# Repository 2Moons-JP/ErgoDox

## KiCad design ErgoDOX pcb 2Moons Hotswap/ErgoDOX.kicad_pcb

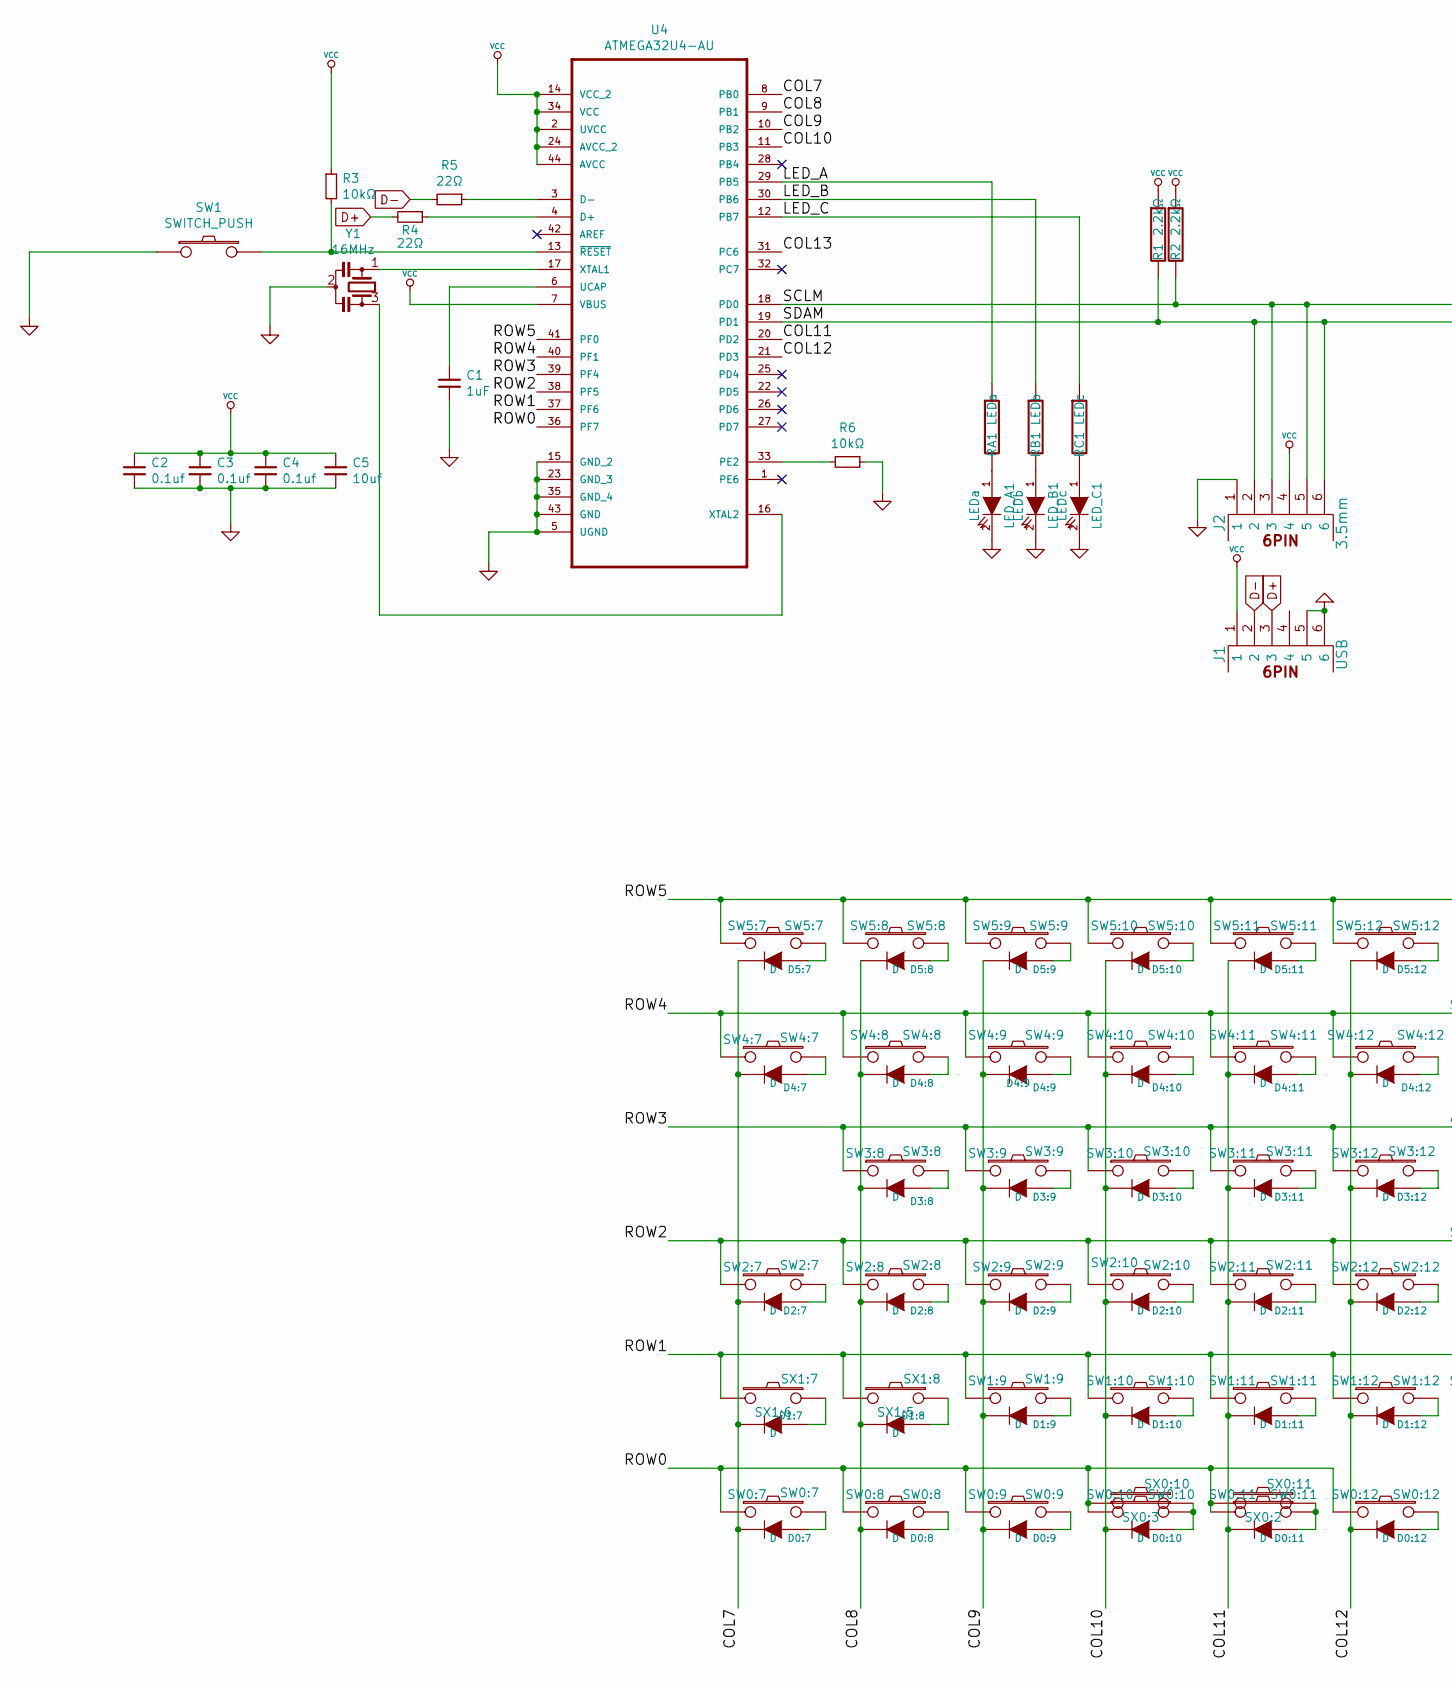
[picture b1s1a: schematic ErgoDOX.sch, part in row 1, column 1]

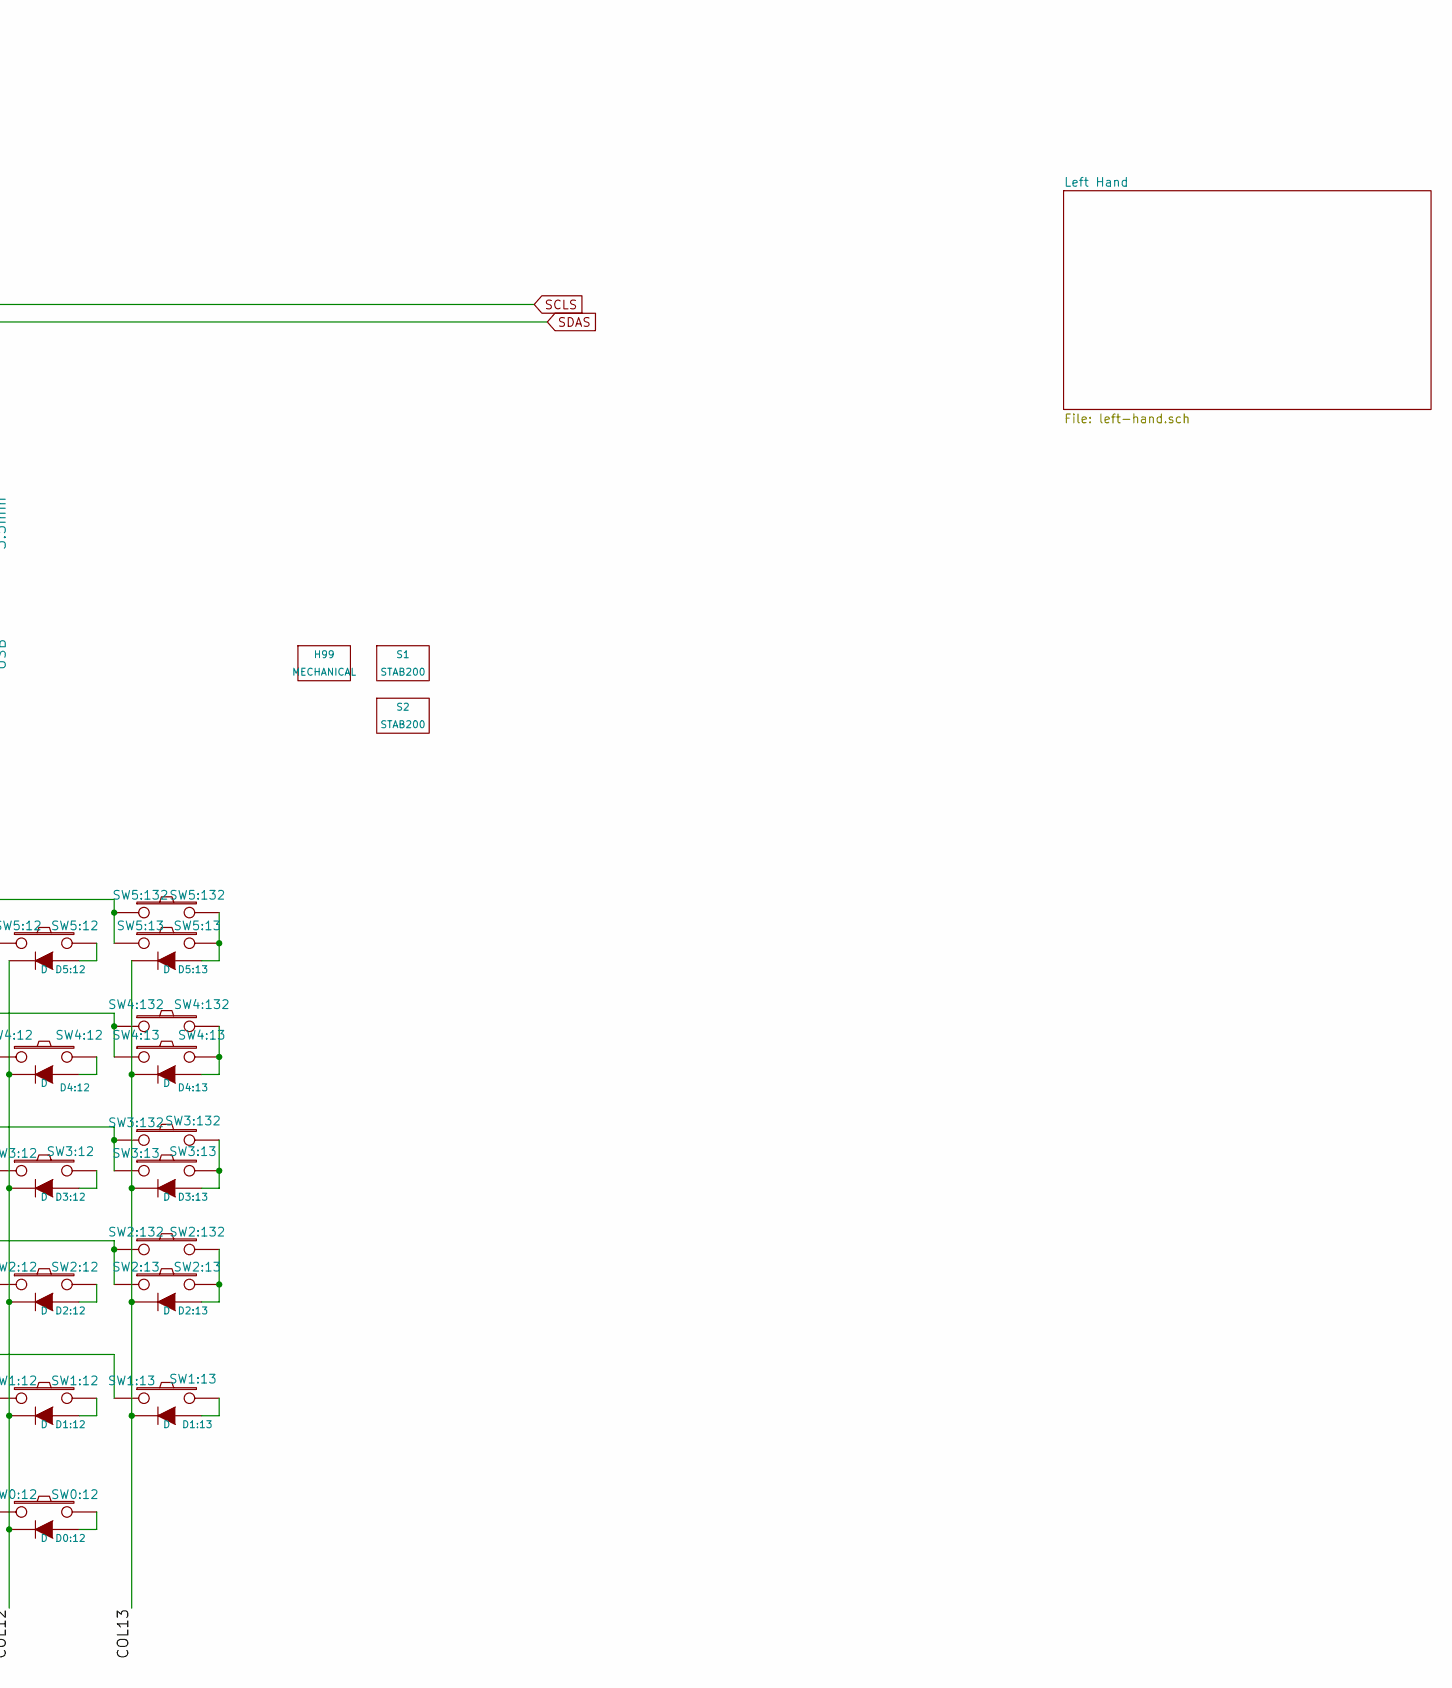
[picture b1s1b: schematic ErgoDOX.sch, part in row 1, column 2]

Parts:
C1: 1uF; C_0603_1608Metric; Part# CL10A105KP8NNNC; LCSC Part# C26413
C2, C3, C4: 0.1uf; C_0603_1608Metric; Part# GRM188R71H104KA93D; LCSC Part# C77055
C5: 10uf; C_0603_1608Metric; Part# JMK107ABJ106MA-T; LCSC Part# C268008
D0:7, D0:8, D0:9, D0:10, D0:11, D0:12, D1:7, D1:8, D1:9, D1:10, D1:11, D1:12, D1:13, D2:7, D2:8, D2:9, D2:10, D2:11, D2:12, D2:13, D3:8, D3:9, D3:10, D3:11, D3:12, D3:13, D4:7, D4:8, D4:10, D4:11, D4:12, D4:13, D5:7, D5:8, D5:9, D5:10, D5:11, D5:12, D5:13: D; D3_SMD_v2_copy; Part# 1N4148W; LCSC Part# C81598
D4:9: D4:9; D3_SMD_v2_copy; Part# 1N4148W; LCSC Part# C81598
H99: MECHANICAL
J1: USB; USBMINImod; Part# 548190519; LCSC Part# C240850
J2: 3.5mm; 4pin35mmAudio; Part# CP-43514-ND; LCSC Part# SJ-43514
LED_A1: LEDa; MX_LED
LED_B1: LEDb; MX_LED
LED_C1: LEDc; MX_LED
R1, R2: 2.2kΩ; R_0603_1608Metric; Part# 0603WAF2201T5E; LCSC Part# C4190
R3, R6: 10kΩ; R_0603_1608Metric; Part# 0603WAF1002T5E; LCSC Part# C25804
R4, R5: 22Ω; R_0603_1608Metric; Part# RS-03K220JT; LCSC Part# C96423
RA1: LEDa; RESISTOR
RB1: LEDb; RESISTOR
RC1: LEDc; RESISTOR
S1, S2: STAB200
SW0:7: SW0:7; MXOnly-1U-Hotswap
SW0:8: SW0:8; MXOnly-1U-Hotswap
SW0:9: SW0:9; MXOnly-1U-Hotswap
SW0:10: SW0:10; MXOnly-2U-Hotswap
SW0:11: SW0:11; MXOnly-2U-Hotswap-ReversedStabilizers
SW0:12: SW0:12; MXOnly-1U-Hotswap
SW1: SWITCH_PUSH; SKQG-1155865; Part# RS-187R05A2-DSMTRT; LCSC Part# C221929
SW1:9: SW1:9; MXOnly-1U-Hotswap
SW1:10: SW1:10; MXOnly-1U-Hotswap
SW1:11: SW1:11; MXOnly-1U-Hotswap
SW1:12: SW1:12; MXOnly-1U-Hotswap
SW1:13: SW1:13; MXOnly-1U-Hotswap
SW2:7: SW2:7; MXOnly-1U-Hotswap
SW2:8: SW2:8; MXOnly-1U-Hotswap
SW2:9: SW2:9; MXOnly-1U-Hotswap
SW2:10: SW2:10; MXOnly-1U-Hotswap
SW2:11: SW2:11; MXOnly-1U-Hotswap
SW2:12: SW2:12; MXOnly-1U-Hotswap
SW2:13: SW2:13; MXOnly-1.5U-Hotswap
SW2:132: SW2:132; MXOnly-1U-Hotswap
SW3:8: SW3:8; MXOnly-1U-Hotswap
SW3:9: SW3:9; MXOnly-1U-Hotswap
SW3:10: SW3:10; MXOnly-1U-Hotswap
SW3:11: SW3:11; MXOnly-1U-Hotswap
SW3:12: SW3:12; MXOnly-1U-Hotswap
SW3:13: SW3:13; MXOnly-1.5U-Hotswap
SW3:132: SW3:132; MXOnly-1U-Hotswap
SW4:7: SW4:7; MXOnly-1U-Hotswap
SW4:8: SW4:8; MXOnly-1U-Hotswap
SW4:9: SW4:9; MXOnly-1U-Hotswap
SW4:10: SW4:10; MXOnly-1U-Hotswap
SW4:11: SW4:11; MXOnly-1U-Hotswap
SW4:12: SW4:12; MXOnly-1U-Hotswap
SW4:13: SW4:13; MXOnly-1.5U-Hotswap
SW4:132: SW4:132; MXOnly-1U-Hotswap
SW5:7: SW5:7; MXOnly-1U-Hotswap
SW5:8: SW5:8; MXOnly-1U-Hotswap
SW5:9: SW5:9; MXOnly-1U-Hotswap
SW5:10: SW5:10; MXOnly-1U-Hotswap
SW5:11: SW5:11; MXOnly-1U-Hotswap
SW5:12: SW5:12; MXOnly-1U-Hotswap
SW5:13: SW5:13; MXOnly-1.5U-Hotswap
SW5:132: SW5:132; MXOnly-1U-Hotswap
SX0:10: SX0:3; MXOnly-1U-Hotswap
SX0:11: SX0:2; MXOnly-1U-Hotswap
SX1:7: SX1:6; MXOnly-1U-Hotswap
SX1:8: SX1:5; MXOnly-1U-Hotswap
U4: ATMEGA32U4-AU; Part# ATMEGA32U4-AU; LCSC Part# C44854
Y1: 16MHz; Resonator_SMD_muRata_CSTxExxV-3Pin_3.0x1.1mm_HandSoldering_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; Part# CSTNE16M0V530000R0; LCSC Part# C341521

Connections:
/COL7: D0:7.2 (K), D1:7.2 (K), D2:7.2 (K), D4:7.2 (K), D5:7.2 (K), U4.8 (PB0)
/COL8: D0:8.2 (K), D1:8.2 (K), D2:8.2 (K), D3:8.2 (K), D4:8.2 (K), D5:8.2 (K), U4.9 (PB1)
/COL9: D0:9.2 (K), D1:9.2 (K), D2:9.2 (K), D3:9.2 (K), D4:9.2 (K), D5:9.2 (K), U4.10 (PB2)
/COL10: D0:10.2 (K), D1:10.2 (K), D2:10.2 (K), D3:10.2 (K), D4:10.2 (K), D5:10.2 (K), U4.11 (PB3)
/COL11: D0:11.2 (K), D1:11.2 (K), D2:11.2 (K), D3:11.2 (K), D4:11.2 (K), D5:11.2 (K), U4.20 (PD2)
/COL12: D0:12.2 (K), D1:12.2 (K), D2:12.2 (K), D3:12.2 (K), D4:12.2 (K), D5:12.2 (K), U4.21 (PD3)
/COL13: D1:13.2 (K), D2:13.2 (K), D3:13.2 (K), D4:13.2 (K), D5:13.2 (K), U4.31 (PC6)
/LED_A: RA1.1, U4.29 (PB5)
/LED_B: RB1.1, U4.30 (PB6)
/LED_C: RC1.1, U4.12 (PB7)
/ROW0: SW0:7.1, SW0:8.1, SW0:9.1, SW0:10.1, SW0:11.1, SW0:12.1, SX0:10.1, SX0:11.1, U4.36 (PF7)
/ROW1: SW1:9.1, SW1:10.1, SW1:11.1, SW1:12.1, SW1:13.1, SX1:7.1, SX1:8.1, U4.37 (PF6)
/ROW2: SW2:7.1, SW2:8.1, SW2:9.1, SW2:10.1, SW2:11.1, SW2:12.1, SW2:13.1, SW2:132.1, U4.38 (PF5)
/ROW3: SW3:8.1, SW3:9.1, SW3:10.1, SW3:11.1, SW3:12.1, SW3:13.1, SW3:132.1, U4.39 (PF4)
/ROW4: SW4:7.1, SW4:8.1, SW4:9.1, SW4:10.1, SW4:11.1, SW4:12.1, SW4:13.1, SW4:132.1, U4.40 (PF1)
/ROW5: SW5:7.1, SW5:8.1, SW5:9.1, SW5:10.1, SW5:11.1, SW5:12.1, SW5:13.1, SW5:132.1, U4.41 (PF0)
D+: J1.3, R4.2; also elsewhere on the board
D-: J1.2, R5.2; also elsewhere on the board
GND: C1.2, C2.2, C3.2, C4.2, C5.2, J1.5, J1.6, J2.1, LED_A1.2 (K), LED_B1.2 (K), LED_C1.2 (K), R6.1, SW1.1, U4.5 (UGND), U4.15 (GND_2), U4.23 (GND_3), U4.35 (GND_4), U4.43 (GND), Y1.2; also elsewhere on the board
unnamed: C1.1, U4.6 (UCAP)
unnamed: D0:7.1 (A), SW0:7.2
unnamed: D0:8.1 (A), SW0:8.2
unnamed: D0:9.1 (A), SW0:9.2
unnamed: D0:10.1 (A), SW0:10.2, SX0:10.2
unnamed: D0:11.1 (A), SW0:11.2, SX0:11.2
unnamed: D0:12.1 (A), SW0:12.2
unnamed: D1:7.1 (A), SX1:7.2
unnamed: D1:8.1 (A), SX1:8.2
unnamed: D1:9.1 (A), SW1:9.2
unnamed: D1:10.1 (A), SW1:10.2
unnamed: D1:11.1 (A), SW1:11.2
unnamed: D1:12.1 (A), SW1:12.2
unnamed: D1:13.1 (A), SW1:13.2
unnamed: D2:7.1 (A), SW2:7.2
unnamed: D2:8.1 (A), SW2:8.2
unnamed: D2:9.1 (A), SW2:9.2
unnamed: D2:10.1 (A), SW2:10.2
unnamed: D2:11.1 (A), SW2:11.2
unnamed: D2:12.1 (A), SW2:12.2
unnamed: D2:13.1 (A), SW2:13.2, SW2:132.2
unnamed: D3:8.1 (A), SW3:8.2
unnamed: D3:9.1 (A), SW3:9.2
unnamed: D3:10.1 (A), SW3:10.2
unnamed: D3:11.1 (A), SW3:11.2
unnamed: D3:12.1 (A), SW3:12.2
unnamed: D3:13.1 (A), SW3:13.2, SW3:132.2
unnamed: D4:7.1 (A), SW4:7.2
unnamed: D4:8.1 (A), SW4:8.2
unnamed: D4:9.1 (A), SW4:9.2
unnamed: D4:10.1 (A), SW4:10.2
unnamed: D4:11.1 (A), SW4:11.2
unnamed: D4:12.1 (A), SW4:12.2
unnamed: D4:13.1 (A), SW4:13.2, SW4:132.2
unnamed: D5:7.1 (A), SW5:7.2
unnamed: D5:8.1 (A), SW5:8.2
unnamed: D5:9.1 (A), SW5:9.2
unnamed: D5:10.1 (A), SW5:10.2
unnamed: D5:11.1 (A), SW5:11.2
unnamed: D5:12.1 (A), SW5:12.2
unnamed: D5:13.1 (A), SW5:13.2, SW5:132.2
unnamed 115: J1.4; also elsewhere on the board
unnamed: LED_A1.1 (A), RA1.2
unnamed: LED_B1.1 (A), RB1.2
unnamed: LED_C1.1 (A), RC1.2
unnamed: R3.2, SW1.2, U4.13 (~RESET)
unnamed: R4.1, U4.4 (D+)
unnamed: R5.1, U4.3 (D-)
unnamed: R6.2, U4.33 (PE2)
unnamed: U4.16 (XTAL2), Y1.3
unnamed: U4.17 (XTAL1), Y1.1
SCLS: J2.3, J2.5, R2.2, U4.18 (PD0); also elsewhere on the board
SDAS: J2.2, J2.6, R1.2, U4.19 (PD1); also elsewhere on the board
VCC: C2.1, C3.1, C4.1, C5.1, J1.1, J2.4, R1.1, R2.1, R3.1, U4.2 (UVCC), U4.7 (VBUS), U4.14 (VCC_2), U4.24 (AVCC_2), U4.34 (VCC), U4.44 (AVCC); also elsewhere on the board

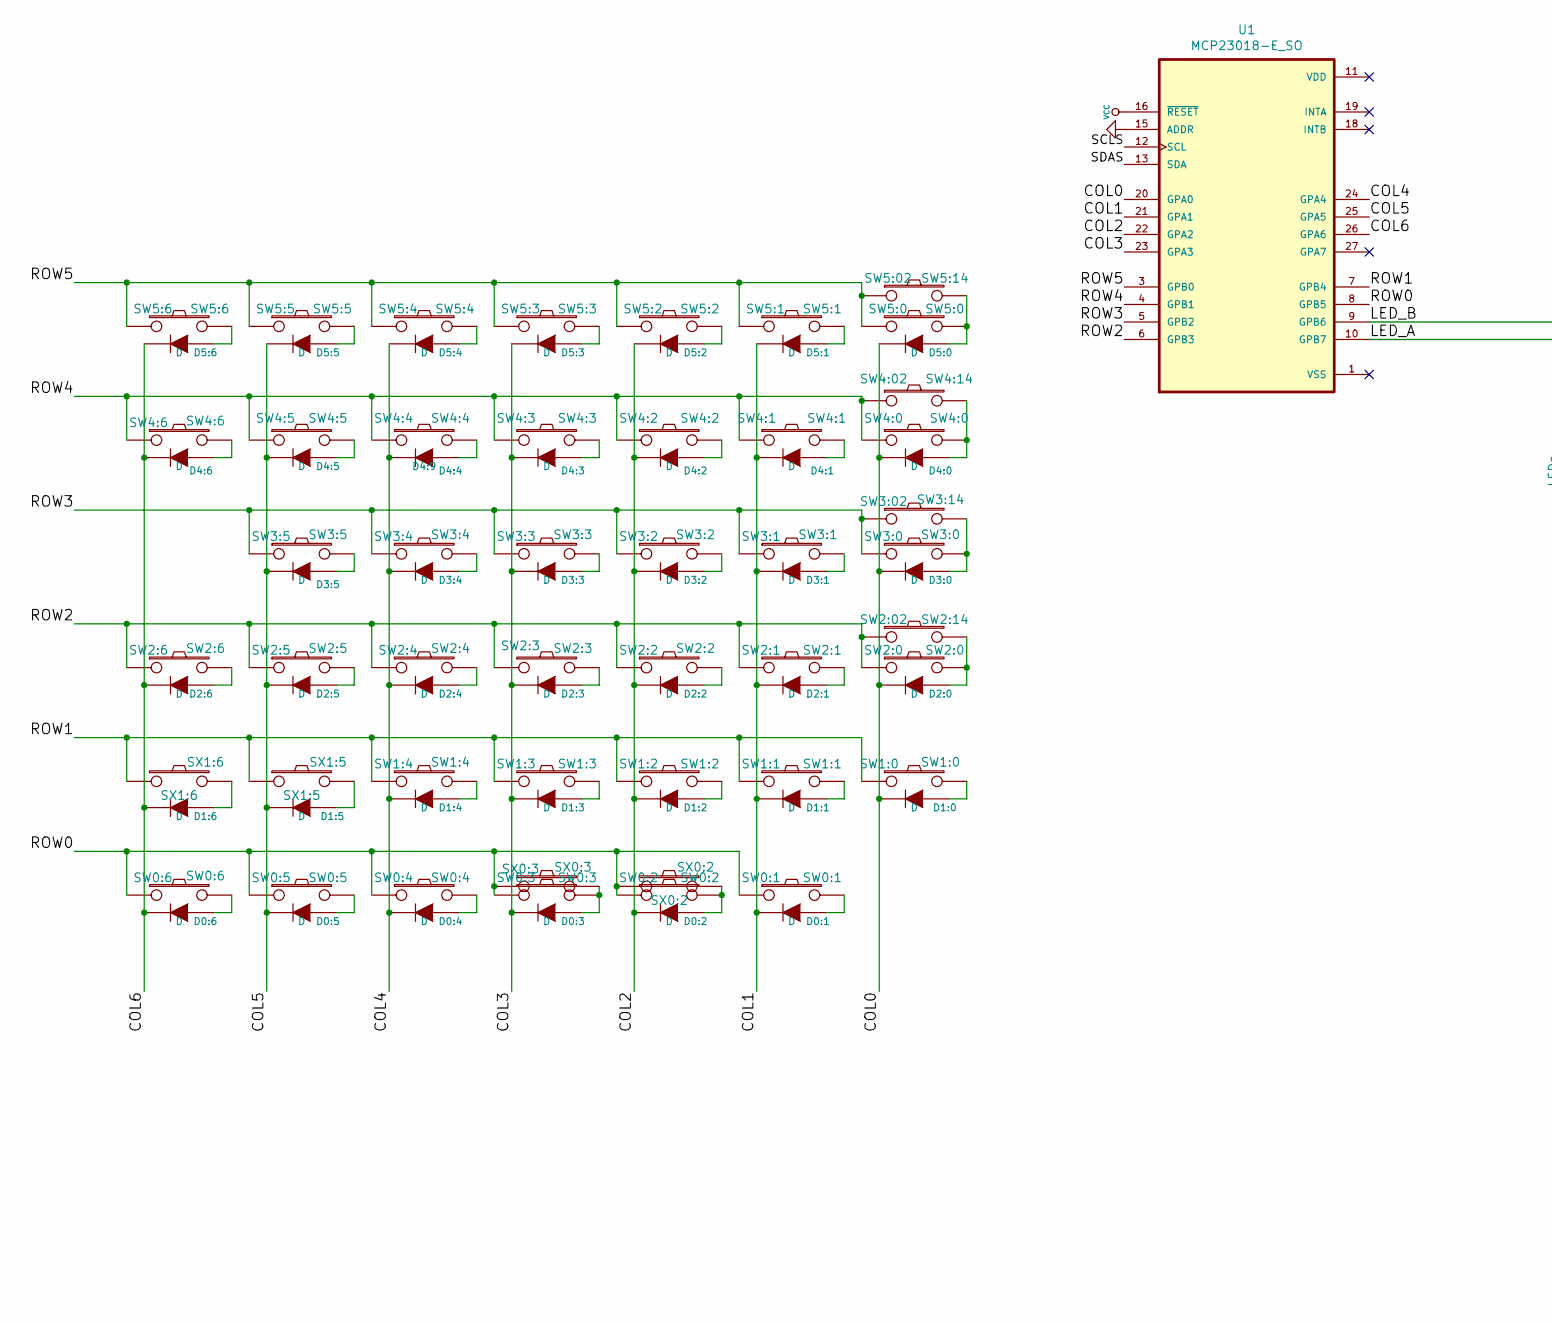
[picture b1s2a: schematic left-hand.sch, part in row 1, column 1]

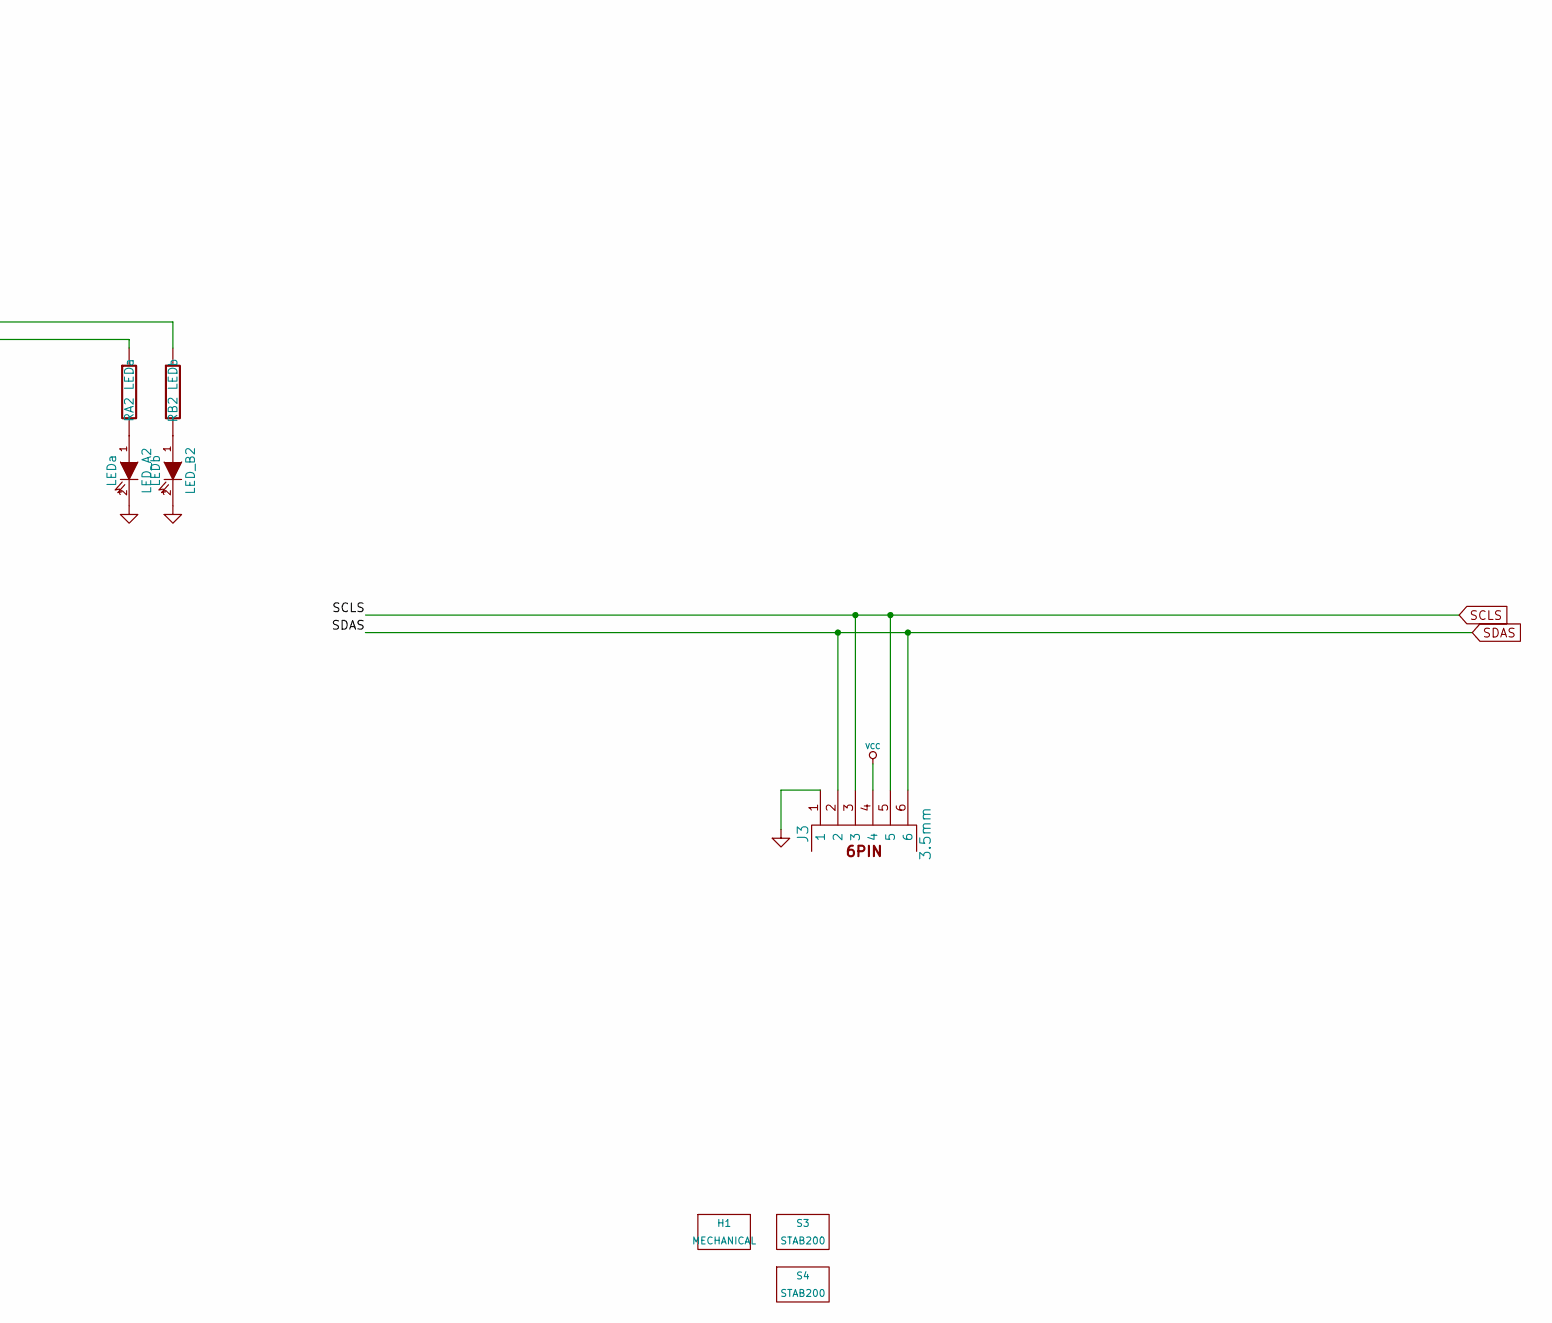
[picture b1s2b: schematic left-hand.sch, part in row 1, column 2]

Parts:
D0:1, D0:2, D0:3, D0:4, D0:5, D0:6, D1:0, D1:1, D1:2, D1:3, D1:4, D1:5, D1:6, D2:0, D2:1, D2:2, D2:3, D2:4, D2:5, D2:6, D3:0, D3:1, D3:2, D3:3, D3:4, D3:5, D4:0, D4:1, D4:2, D4:3, D4:5, D4:6, D5:0, D5:1, D5:2, D5:3, D5:4, D5:5, D5:6: D; D3_SMD_v2_copy; Part# 1N4148W; LCSC Part# C81598
D4:4: D4:9; D3_SMD_v2_copy; Part# 1N4148W; LCSC Part# C81598
H1: MECHANICAL
J3: 3.5mm; 4pin35mmAudio; Part# CP-43514-ND; LCSC Part# SJ-43514
LED_A2: LEDa; MX_LED
LED_B2: LEDb; MX_LED
RA2: LEDa; RESISTOR
RB2: LEDb; RESISTOR
S3, S4: STAB200
SW0:1: SW0:1; MXOnly-1U-Hotswap
SW0:2: SW0:2; MXOnly-2U-Hotswap-ReversedStabilizers
SW0:3: SW0:3; MXOnly-2U-Hotswap
SW0:4: SW0:4; MXOnly-1U-Hotswap
SW0:5: SW0:5; MXOnly-1U-Hotswap
SW0:6: SW0:6; MXOnly-1U-Hotswap
SW1:0: SW1:0; MXOnly-1U-Hotswap
SW1:1: SW1:1; MXOnly-1U-Hotswap
SW1:2: SW1:2; MXOnly-1U-Hotswap
SW1:3: SW1:3; MXOnly-1U-Hotswap
SW1:4: SW1:4; MXOnly-1U-Hotswap
SW2:0: SW2:0; MXOnly-1.5U-Hotswap
SW2:1: SW2:1; MXOnly-1U-Hotswap
SW2:2: SW2:2; MXOnly-1U-Hotswap
SW2:3: SW2:3; MXOnly-1U-Hotswap
SW2:4: SW2:4; MXOnly-1U-Hotswap
SW2:5: SW2:5; MXOnly-1U-Hotswap
SW2:6: SW2:6; MXOnly-1U-Hotswap
SW2:14: SW2:02; MXOnly-1U-Hotswap
SW3:0: SW3:0; MXOnly-1.5U-Hotswap
SW3:1: SW3:1; MXOnly-1U-Hotswap
SW3:2: SW3:2; MXOnly-1U-Hotswap
SW3:3: SW3:3; MXOnly-1U-Hotswap
SW3:4: SW3:4; MXOnly-1U-Hotswap
SW3:5: SW3:5; MXOnly-1U-Hotswap
SW3:14: SW3:02; MXOnly-1U-Hotswap
SW4:0: SW4:0; MXOnly-1.5U-Hotswap
SW4:1: SW4:1; MXOnly-1U-Hotswap
SW4:2: SW4:2; MXOnly-1U-Hotswap
SW4:3: SW4:3; MXOnly-1U-Hotswap
SW4:4: SW4:4; MXOnly-1U-Hotswap
SW4:5: SW4:5; MXOnly-1U-Hotswap
SW4:6: SW4:6; MXOnly-1U-Hotswap
SW4:14: SW4:02; MXOnly-1U-Hotswap
SW5:0: SW5:0; MXOnly-1.5U-Hotswap
SW5:1: SW5:1; MXOnly-1U-Hotswap
SW5:2: SW5:2; MXOnly-1U-Hotswap
SW5:3: SW5:3; MXOnly-1U-Hotswap
SW5:4: SW5:4; MXOnly-1U-Hotswap
SW5:5: SW5:5; MXOnly-1U-Hotswap
SW5:6: SW5:6; MXOnly-1U-Hotswap
SW5:14: SW5:02; MXOnly-1U-Hotswap
SX0:2: SX0:2; MXOnly-1U-Hotswap
SX0:3: SX0:3; MXOnly-1U-Hotswap
SX1:5: SX1:5; MXOnly-1U-Hotswap
SX1:6: SX1:6; MXOnly-1U-Hotswap
U1: MCP23018-E_SO; SOIC127P1030X265-28N; PARTREV A

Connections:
/Left Hand/COL0: D1:0.2 (K), D2:0.2 (K), D3:0.2 (K), D4:0.2 (K), D5:0.2 (K), U1.20 (GPA0)
/Left Hand/COL1: D0:1.2 (K), D1:1.2 (K), D2:1.2 (K), D3:1.2 (K), D4:1.2 (K), D5:1.2 (K), U1.21 (GPA1)
/Left Hand/COL2: D0:2.2 (K), D1:2.2 (K), D2:2.2 (K), D3:2.2 (K), D4:2.2 (K), D5:2.2 (K), U1.22 (GPA2)
/Left Hand/COL3: D0:3.2 (K), D1:3.2 (K), D2:3.2 (K), D3:3.2 (K), D4:3.2 (K), D5:3.2 (K), U1.23 (GPA3)
/Left Hand/COL4: D0:4.2 (K), D1:4.2 (K), D2:4.2 (K), D3:4.2 (K), D4:4.2 (K), D5:4.2 (K), U1.24 (GPA4)
/Left Hand/COL5: D0:5.2 (K), D1:5.2 (K), D2:5.2 (K), D3:5.2 (K), D4:5.2 (K), D5:5.2 (K), U1.25 (GPA5)
/Left Hand/COL6: D0:6.2 (K), D1:6.2 (K), D2:6.2 (K), D4:6.2 (K), D5:6.2 (K), U1.26 (GPA6)
/Left Hand/LED_A: RA2.1, U1.10 (GPB7)
/Left Hand/LED_B: RB2.1, U1.9 (GPB6)
/Left Hand/ROW0: SW0:1.1, SW0:2.1, SW0:3.1, SW0:4.1, SW0:5.1, SW0:6.1, SX0:2.1, SX0:3.1, U1.8 (GPB5)
/Left Hand/ROW1: SW1:0.1, SW1:1.1, SW1:2.1, SW1:3.1, SW1:4.1, SX1:5.1, SX1:6.1, U1.7 (GPB4)
/Left Hand/ROW2: SW2:0.1, SW2:1.1, SW2:2.1, SW2:3.1, SW2:4.1, SW2:5.1, SW2:6.1, SW2:14.1, U1.6 (GPB3)
/Left Hand/ROW3: SW3:0.1, SW3:1.1, SW3:2.1, SW3:3.1, SW3:4.1, SW3:5.1, SW3:14.1, U1.5 (GPB2)
/Left Hand/ROW4: SW4:0.1, SW4:1.1, SW4:2.1, SW4:3.1, SW4:4.1, SW4:5.1, SW4:6.1, SW4:14.1, U1.4 (GPB1)
/Left Hand/ROW5: SW5:0.1, SW5:1.1, SW5:2.1, SW5:3.1, SW5:4.1, SW5:5.1, SW5:6.1, SW5:14.1, U1.3 (GPB0)
GND: J3.1, LED_A2.2 (K), LED_B2.2 (K), U1.15 (ADDR); also elsewhere on the board
unnamed: D0:1.1 (A), SW0:1.2
unnamed: D0:2.1 (A), SW0:2.2, SX0:2.2
unnamed: D0:3.1 (A), SW0:3.2, SX0:3.2
unnamed: D0:4.1 (A), SW0:4.2
unnamed: D0:5.1 (A), SW0:5.2
unnamed: D0:6.1 (A), SW0:6.2
unnamed: D1:0.1 (A), SW1:0.2
unnamed: D1:1.1 (A), SW1:1.2
unnamed: D1:2.1 (A), SW1:2.2
unnamed: D1:3.1 (A), SW1:3.2
unnamed: D1:4.1 (A), SW1:4.2
unnamed: D1:5.1 (A), SX1:5.2
unnamed: D1:6.1 (A), SX1:6.2
unnamed: D2:0.1 (A), SW2:0.2, SW2:14.2
unnamed: D2:1.1 (A), SW2:1.2
unnamed: D2:2.1 (A), SW2:2.2
unnamed: D2:3.1 (A), SW2:3.2
unnamed: D2:4.1 (A), SW2:4.2
unnamed: D2:5.1 (A), SW2:5.2
unnamed: D2:6.1 (A), SW2:6.2
unnamed: D3:0.1 (A), SW3:0.2, SW3:14.2
unnamed: D3:1.1 (A), SW3:1.2
unnamed: D3:2.1 (A), SW3:2.2
unnamed: D3:3.1 (A), SW3:3.2
unnamed: D3:4.1 (A), SW3:4.2
unnamed: D3:5.1 (A), SW3:5.2
unnamed: D4:0.1 (A), SW4:0.2, SW4:14.2
unnamed: D4:1.1 (A), SW4:1.2
unnamed: D4:2.1 (A), SW4:2.2
unnamed: D4:3.1 (A), SW4:3.2
unnamed: D4:4.1 (A), SW4:4.2
unnamed: D4:5.1 (A), SW4:5.2
unnamed: D4:6.1 (A), SW4:6.2
unnamed: D5:0.1 (A), SW5:0.2, SW5:14.2
unnamed: D5:1.1 (A), SW5:1.2
unnamed: D5:2.1 (A), SW5:2.2
unnamed: D5:3.1 (A), SW5:3.2
unnamed: D5:4.1 (A), SW5:4.2
unnamed: D5:5.1 (A), SW5:5.2
unnamed: D5:6.1 (A), SW5:6.2
unnamed: LED_A2.1 (A), RA2.2
unnamed: LED_B2.1 (A), RB2.2
SCLS: J3.3, J3.5, U1.12 (SCL); also elsewhere on the board
SDAS: J3.2, J3.6, U1.13 (SDA); also elsewhere on the board
VCC: J3.4, U1.16 (~RESET); also elsewhere on the board

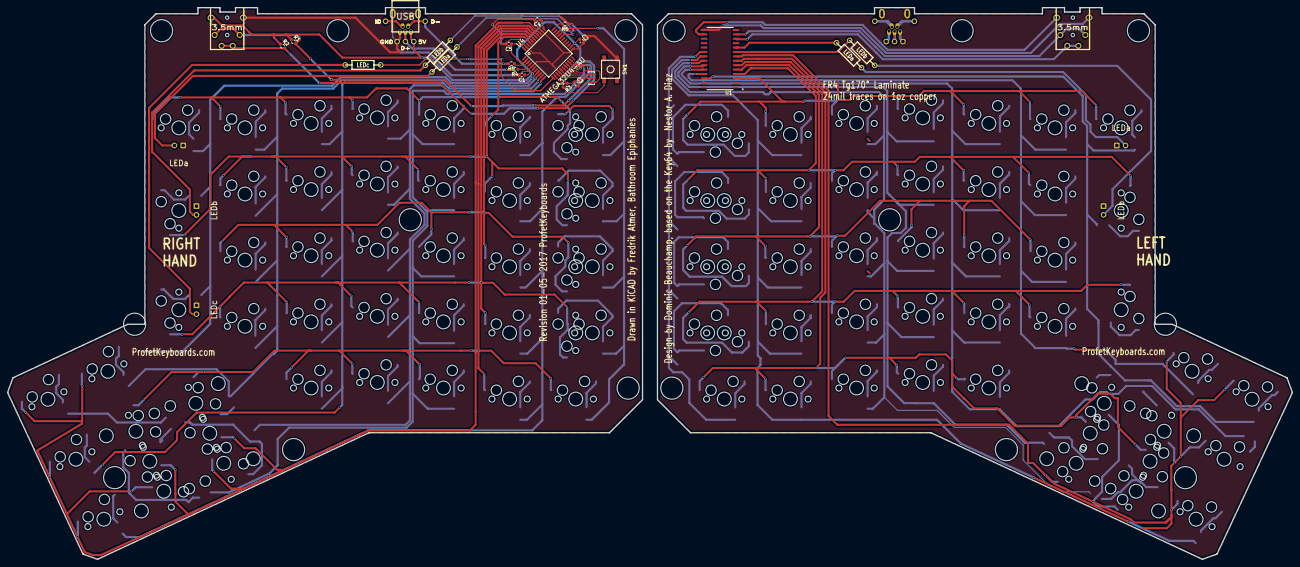
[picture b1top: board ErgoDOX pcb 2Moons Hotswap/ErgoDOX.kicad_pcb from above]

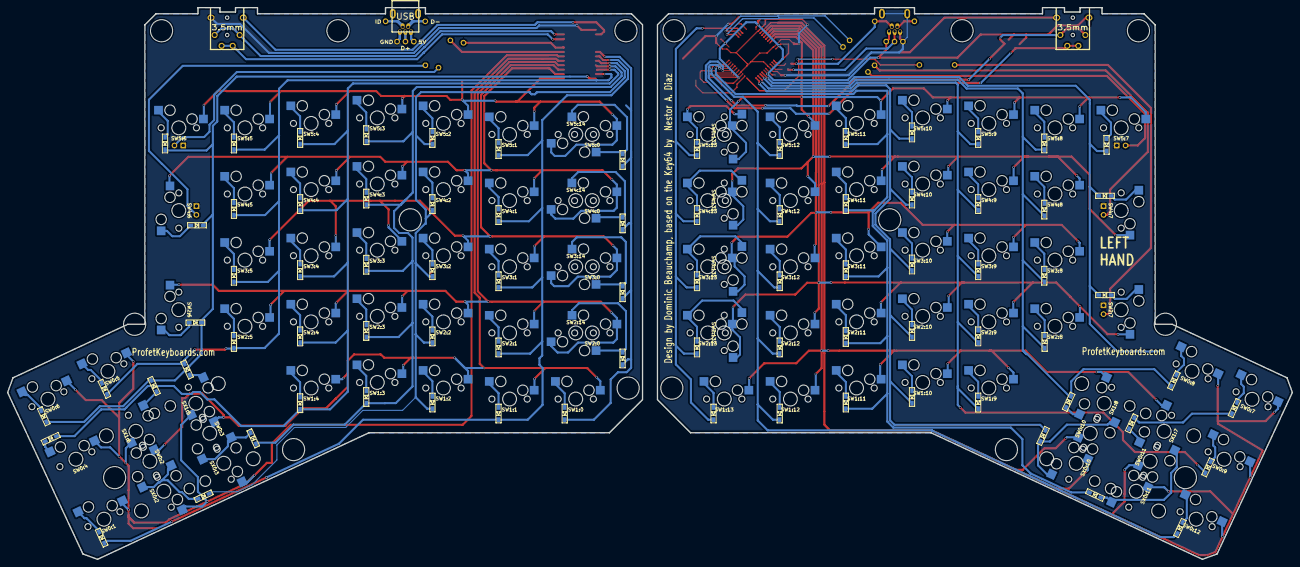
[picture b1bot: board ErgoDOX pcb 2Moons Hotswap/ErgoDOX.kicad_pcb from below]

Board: 2 copper layers, 370.0 x 158.9 mm, 203 parts (82 on the bottom side), 130 nets.

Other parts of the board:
H99#2: MECHANICAL; ErgoDOXmech
J1#2: USB; USBMINImod

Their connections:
D+: J1#2.3; also elsewhere on the board
D-: J1#2.2; also elsewhere on the board
GND: J1#2.5, J1#2.6; also elsewhere on the board
unnamed 115: J1#2.4; also elsewhere on the board
VCC: J1#2.1; also elsewhere on the board
